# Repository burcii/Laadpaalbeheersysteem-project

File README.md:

# Laadpaal Management Systeem

> Schoolproject in groepsverband.

Dit project is een webapplicatie voor het beheren van laadpalen. De applicatie bestaat uit een Python backend en een PHP frontend, met een MySQL-database.

## Vereisten
- Python 3.12+
- Docker Desktop
- Browser

## Starten
### 1. Start de database
```bash
docker compose up -d
```

### 2. Installeer backend-afhankelijkheden
```bash
cd backend
python -m pip install --user -r requirements.txt
```

### 3. Maak de configuratie aan
Maak in `backend/config/` een bestand `config.py` en kopieer de inhoud van `config.py.example` naar dit bestand. Vul daarna de juiste waarden in.

### 4. Start de backend
```bash
cd backend
python server.py
```

De backend draait dan op: http://localhost:8000

### 5. Open de frontend
Open in je browser:
```text
http://localhost
```

Als alles goed werkt, verschijnt de inlogpagina van het project.

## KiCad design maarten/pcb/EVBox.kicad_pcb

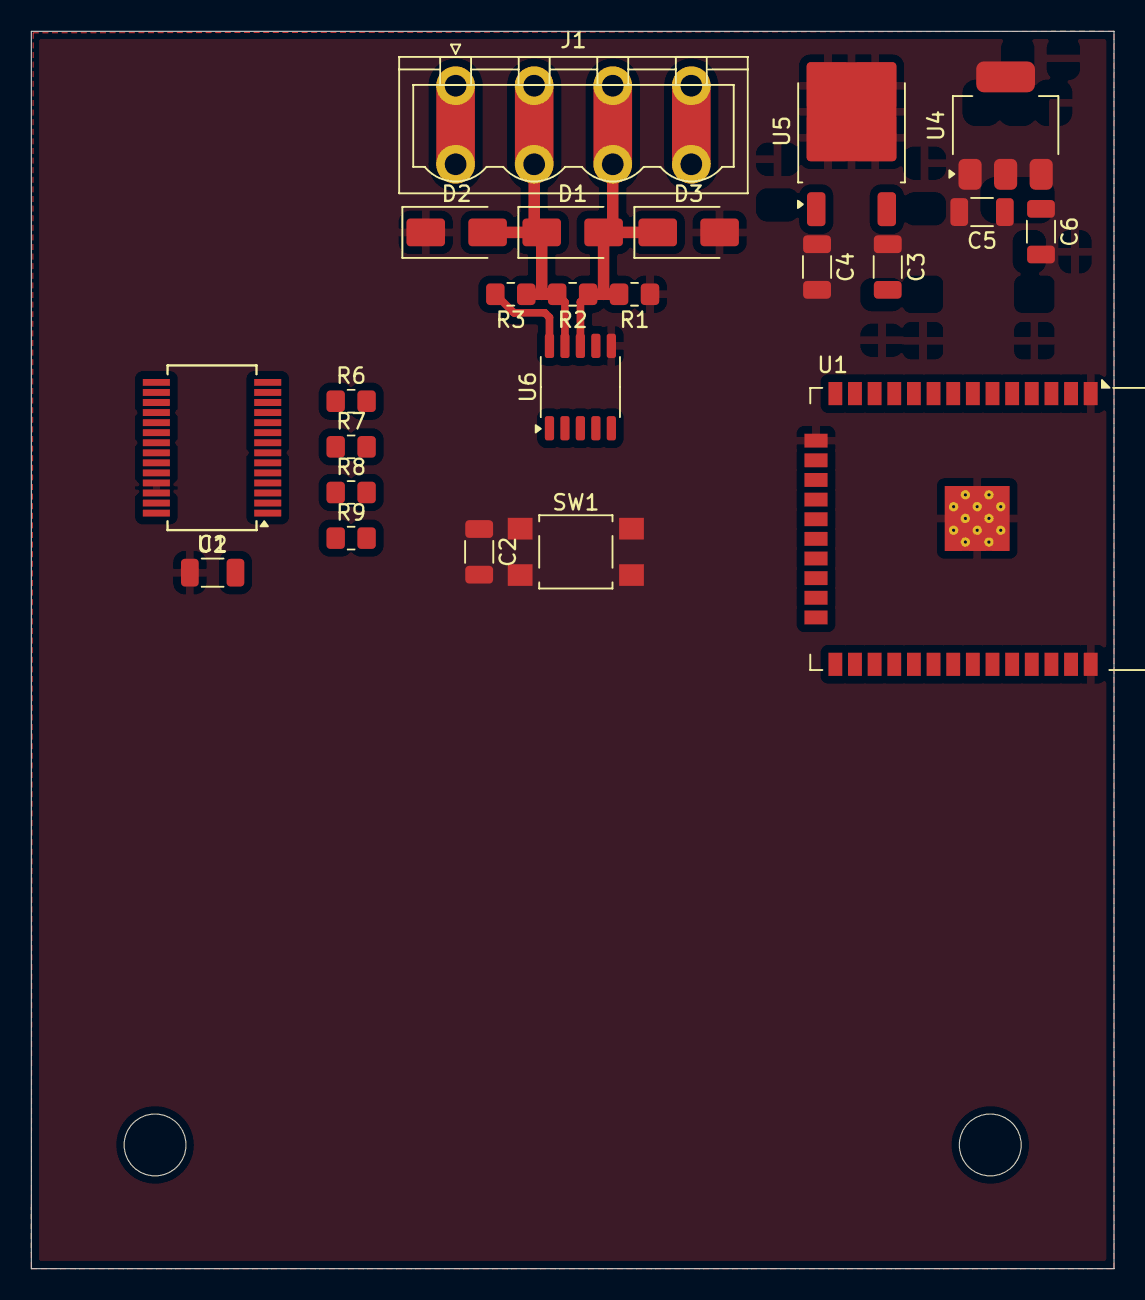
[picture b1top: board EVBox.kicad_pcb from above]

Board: 2 copper layers, 70.0 x 80.0 mm, 23 parts (0 on the bottom side), 17 nets.

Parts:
C1, C2: 100n; C_1206_3216Metric
C3, C4, C5, C6: 10u; C_1206_3216Metric
D1, D2, D3: SMAJ12CA; D_SMA
J1: Conn_01x04_Pin; PhoenixContact_ICV_2,5_4-G-5,08_1x04_P5.08mm_Vertical
R1, R3: 560; R_0805_2012Metric_Pad1.20x1.40mm_HandSolder
R2: 120; R_0805_2012Metric_Pad1.20x1.40mm_HandSolder
R6, R7, R8, R9: 10k; R_0805_2012Metric_Pad1.20x1.40mm_HandSolder
SW1: reset; SW_SPST_TL3305A
U1: ESP32-WROOM-32
U2: FT232RL; SSOP-28_5.3x10.2mm_P0.65mm
U4: AMS1117-3.3; SOT-223-3_TabPin2
U5: L7805; TO-252-2
U6: SOIC-10_3.9x4.9mm_P1mm

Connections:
+3.3V: C5.1, R8.1, R9.2, U1.2 (VDD), U4.2 (VO), U6.1 (Vio)
+5V: C3.1, R3.2, U5.3 (OUT), U6.10 (VCC)
+12V: C4.1, J1.1, U5.1 (IN)
/vccio: C1.2, U2.4 (VCCIO), U2.17 (3V3OUT)
GND: C1.1, C2.2, C3.2, C4.2, C5.2, C6.2, D2.1 (A1), D3.2 (A2), R1.1, SW1.2, U1.1 (GND), U1.15 (GND), U1.38 (GND), U1.39 (GND), U2.7 (GND), U2.18 (GND), U2.21 (GND), U2.25 (AGND), U2.26 (TEST), U4.1 (GND), U5.2 (GND), U6.6 (GND)
unnamed: D1.1 (A1), D2.2 (A2), J1.3, R2.2, R3.1, U6.9 (B)
unnamed: D1.2 (A2), D3.1 (A1), J1.2, R1.2, R2.1, U6.8 (A)
unnamed: C6.1, U4.3 (VI)
unnamed: R6.1, U2.2 (DTR)
unnamed: R7.1, U2.3 (RTS)
boot: R9.1, U1.25 (IO0)
reset: C2.1, R8.2, SW1.1, U1.3 (EN)
rts1: U1.19 (SCS/CMD), U6.3 (DE), U6.4 (~RE)
rxd0: U1.34 (RXD0/IO3), U2.1 (TXD)
rxd1: U1.17 (SHD/SD2), U6.2 (RO)
txd0: U1.35 (TXD0/IO1), U2.5 (RXD)
txd1: U1.18 (SWP/SD3), U6.5 (DI)
